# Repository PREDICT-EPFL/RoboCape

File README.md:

# RoboCape

This repository is dedicated to a Beaglebone cape extension developped at EPFL in the Automatic Control Laboratory.
The idea of this platform is to allow the user to transform any mechanically actuated platform, for example a RC car or a quadcopter base, into a robotic vehicle that can be controlled by a remote server.

The repository contains all the design files of the Beaglebone cape extension.
* Schematic
* PCB layout
* Production files
* Documentation files (useful documents and datasheets)

## Finished board

## License

This project is released under the Creative Commons CC-BY-4.0 license.
See http://creativecommons.org/licenses/by/4.0/ for details.

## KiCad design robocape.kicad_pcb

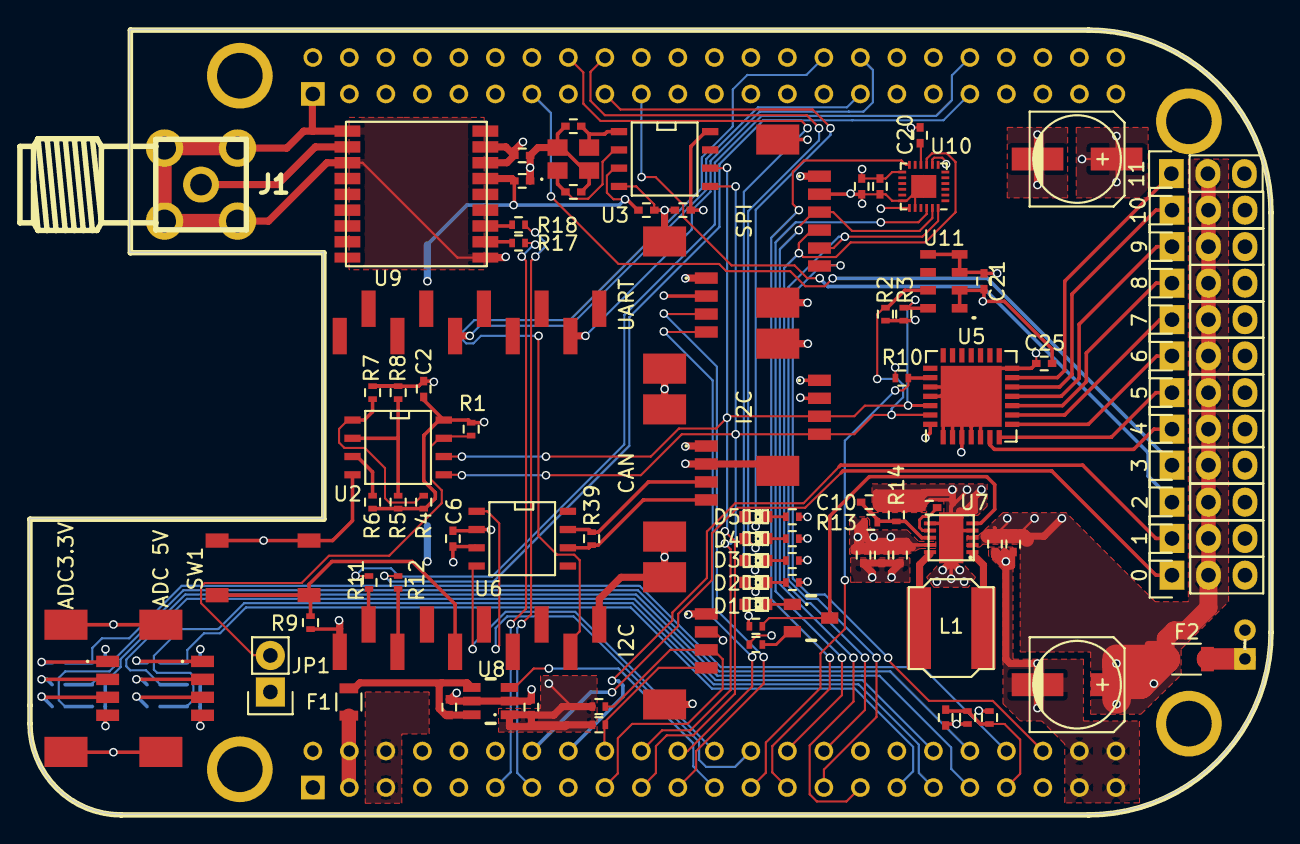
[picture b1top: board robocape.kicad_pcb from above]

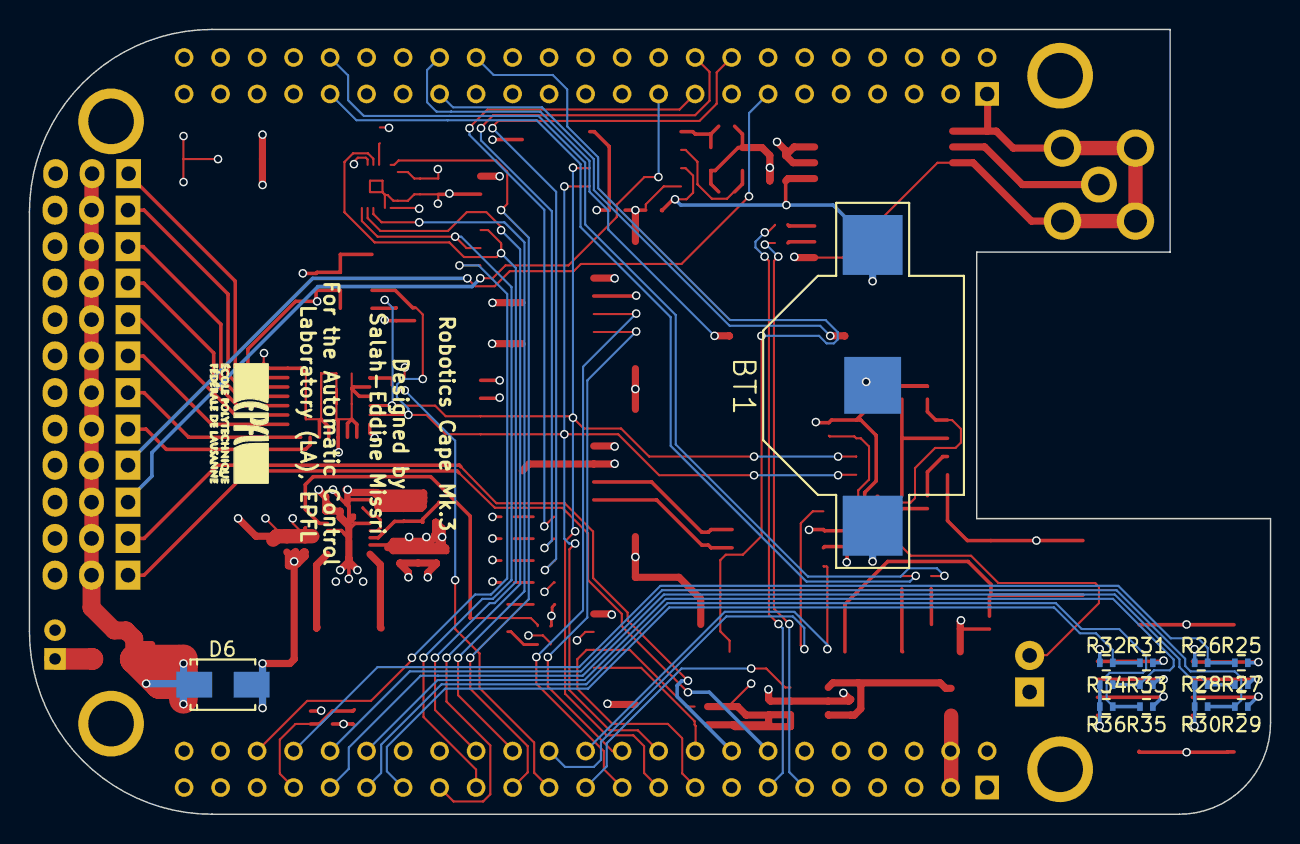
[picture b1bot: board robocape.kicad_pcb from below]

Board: 4 copper layers, 86.4 x 54.6 mm, 110 parts (14 on the bottom side), 85 nets.

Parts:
0, 1, 2, 3, 4, 5, 6, 7, 8, 9, 10, 11: SERVO; Pin_Header_Straight_1x03
BT1: 1.4V to 3.6V; BK-885
C1, C14, C15: 1u; C_0402
C2, C6, C9, C17, C20, C21, C22, C25: 100n; C_0402
C3: 220n; C_0402
C4, C5, C10: 10p; C_0402
C7, C8: 10u; C_0402
C11, C12, C13: 22u; C_0402
C16, C19: 0.1u; C_0402
C18: 10n; C_0402
C23, C24: 100u; c_elec_6.3x7.7
CONN1: UART; _Molex-PicoBlade-SMD-4
CONN5, CONN17: I2C; _Molex-PicoBlade-SMD-4
CONN9: CAN; _Molex-PicoBlade-SMD-4
CONN16: PWR; _Pin2mm_2
CONN18: SPI; _Molex-PicoBlade-SMD-6
CONN19: ADC3.3V; _Molex-PicoBlade-SMD-4
CONN20: ADC 5V; _Molex-PicoBlade-SMD-4
D1: YELLOW; LED-0603
D2: WHITE; LED-0603
D3: GREEN; LED-0603
D4: BLUE; LED-0603
D5: RED; LED-0603
D6: ZENER 12V; Diode-SMA_Standard
F1: 500mA; R_0805
F2: 10A; R_1206
J1: SMA; SMA-CONN
JP1: Jumper_NC_Small; Pin_Header_Straight_1x02
L1: 1uH; Laird_TYS6045
Q1: 2N7002; _SOT23-3
R1, R10: 10k; R_0402
R2, R3, R4, R5, R6, R23, R24, R37: 4.7k; R_0402
R7, R8: 0; R_0402
R9: 50k; R_0402
R11, R12, R17, R18: 330; R_0402
R13, R15: 1M; R_0402
R14: 111k; R_0402
R16, R19, R20, R21, R22: 1k; R_0402
R25, R27, R29: 680; R_0402
R26, R28, R30, R32, R34, R36, R38: 820; R_0402
R31, R33, R35: 1.47k; R_0402
R39: 120; R_0402
SW1: SW_PUSH; _PTS525SK15-SMT-Pushbutton
U1: BEAGLEBONE
U2: CAT24C256W; SOIC-8-N
U3: BQ32000; SOIC-8-N
U4: XBee_Header; Xbee_Header_SMD
U5: PCA9685; QFN-28-1EP_6x6mm_Pitch0.65mm
U6: SN65HVD232D; SOIC-8-N
U7: TPS63060; SON-10
U8: TPS22929D; _TSOT23-6
U9: MAX-M8
U10: MPU-9250; QFN-24-1EP_3x3mm_Pitch0.4mm
U11: MS5611-01BA; _MS5611-01BA
X1: 32768Hz; _TSX-3225-SMD-XTAL

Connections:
+3.3V_A: C1.1, C2.1, C15.1, C17.1, C18.1, C21.1, C25.1, CONN5.1, CONN17.1, D2.2, R1.1, R2.1, R3.1, R4.1, R5.1, R6.1, R10.1, R23.1, R24.1, U2.8, U3.8, U5.28, U8.1, U10.8, U10.13, U10.19, U11.1, U11.2
+3V3: C6.1, C16.1, F1.1, R9.1, U1.C3, U1.C4, U4.1, U6.3, U9.7, U9.8
+5V: C11.1, C12.1, C13.1, CONN1.1, CONN9.1, CONN18.1, D1.2, R13.1, R15.1, U1.C5, U1.C6, U7.9
/Connectivity/ADC_1: R25.2, R26.1, U1.C40
/Connectivity/ADC_2: R27.2, R28.1, U1.C37
/Connectivity/ADC_3: R29.2, R30.1, U1.C38
/Connectivity/ADC_4: R31.2, R32.1, U1.C33
/Connectivity/ADC_5: R33.2, R34.1, U1.C36
/Connectivity/ADC_6: R35.2, R36.1, U1.C35
/Connectivity/CAN_RX: U1.C24, U6.4
/Connectivity/CAN_TX: U1.C26, U6.1
/Connectivity/I2C1_SCL: CONN17.3, R24.2, U1.C17
/Connectivity/I2C1_SDA: CONN17.4, R23.2, U1.C18
/Connectivity/I2C2_SCL: CONN5.3, R3.2, U1.C19, U2.6, U3.6, U5.26, U11.8
/Connectivity/I2C2_SDA: CONN5.4, R2.2, U1.C20, U2.5, U3.5, U5.27, U11.7
/Connectivity/PWMGEN_OE: R10.2, U1.C25, U5.23
/Connectivity/PWM_0: 0.1, U1.C14
/Connectivity/PWM_1: 1.1, U1.C16
/Connectivity/PWM_2: 2.1, U1.B19
/Connectivity/PWM_3: 3.1, U1.B13
/Connectivity/PWM_4: 4.1, U5.6
/Connectivity/PWM_5: 5.1, U5.7
/Connectivity/PWM_6: 6.1, U5.8
/Connectivity/PWM_7: 7.1, U5.9
/Connectivity/PWM_8: 8.1, U5.10
/Connectivity/PWM_9: 9.1, U5.11
/Connectivity/PWM_10: 10.1, U5.12
/Connectivity/PWM_11: 11.1, U5.13
/Connectivity/SPI1_CS1: CONN18.6, U1.C42
/Connectivity/UART_EXT_RX: CONN1.4, U1.C22
/Connectivity/UART_EXT_TX: CONN1.3, U1.C21
/Connectivity/XBEE_CTS: U1.B32, U4.12
/Connectivity/XBEE_DTR: U1.B30, U4.9
/Connectivity/XBEE_RTS: U1.B31, U4.16
/Connectivity/XBEE_RX: R12.1, U1.B37
/Connectivity/XBEE_TX: R11.1, U1.B38
/ERROR_LED: D5.2, U1.B17
/HEARTBEAT_LED: D3.2, U1.B16
/Power/3.3V_A_EN: U1.C23, U8.3
/Power/Back_Bat: BT1.1, C3.1, C19.1, U3.3, U9.6
/Power/PWR_GOOD: Q1.2, R15.2, U7.5
/Power/PWR_VOLTAGE_SENSE: C22.1, R37.2, R38.1, U1.C39
/STATUS_LED: D4.2, U1.B18
/Sensors/GPS_RX: R18.1, U1.C13
/Sensors/GPS_TX: R17.1, U1.C11
/Sensors/MPU9250_CS: U1.C28, U10.22
/Sensors/MPU9250_INT: U1.C27, U10.12
/Sensors/MPU9250_MISO: CONN18.4, U1.C30, U10.9
/Sensors/MPU9250_MOSI: CONN18.5, U1.C29, U10.24
/Sensors/MPU9250_SCK: CONN18.3, U1.C31, U10.23
GND: 0.3, 1.3, 2.3, 3.3, 4.3, 5.3, 6.3, 7.3, 8.3, 9.3, 10.3, 11.3, BT1.2, C1.2, C2.2, C3.2, C4.2, C5.2, C6.2, C7.2, C8.2, C9.2, C10.2, C11.2, C12.2, C13.2, C14.2, C15.2, C16.2, C17.2, C18.2, C19.2, C20.2, C21.2, C22.2, C23.2, C24.2, C25.2, CONN1.2, CONN1.MECH, CONN5.2, CONN5.MECH, CONN9.2, CONN9.MECH, CONN16.2, CONN17.2, CONN17.MECH, CONN18.2, CONN18.MECH, CONN19.4, CONN19.MECH, CONN20.4, CONN20.MECH, D6.2, J1.2, J1.3, J1.4, J1.5, JP1.1, R7.2, R8.2, R14.2, R16.2, R19.1, R20.1, R21.1, R22.1, R26.2, R28.2, R30.2, R32.2, R34.2, R36.2, R38.2, SW1.1, U1.B1, U1.B2, U1.C1, U1.C2, U1.C34, U1.C43, U1.C44, U1.C45, U1.C46, U2.4, U3.4, U4.10, U5.1, U5.2, U5.3, U5.4, U5.5, U5.14, U5.24, U5.25, U5.29, U6.2, U7.4, U7.7, U7.11, U8.2, U8.5, U9.1, U9.10, U9.12, U10.18, U10.20, U10.25, U11.3, U11.4, U11.5, X1.2, X1.4
unnamed: C4.1, U3.2, X1.1
unnamed: C5.1, U3.1, X1.3
unnamed: C9.1, U7.6
unnamed: C10.1, R13.2, R14.1, U7.8
unnamed: C14.1, F1.2, U8.4, U8.6
unnamed: C20.1, U10.10
unnamed: CONN9.3, R39.1, U6.7
unnamed: CONN9.4, R39.2, U6.6
unnamed: CONN16.1, F2.1
unnamed: CONN19.1, R25.1
unnamed: CONN19.2, R27.1
unnamed: CONN19.3, R29.1
unnamed: CONN20.1, R31.1
unnamed: CONN20.2, R33.1
unnamed: CONN20.3, R35.1
unnamed: D1.1, Q1.1
unnamed: D2.1, R19.2
unnamed: D3.1, R20.2
unnamed: D4.1, R21.2
unnamed: D5.1, R22.2
unnamed: J1.1, U9.11
unnamed: JP1.2, R1.2, U2.7
unnamed: L1.1, U7.1
unnamed: L1.2, U7.10
unnamed: Q1.3, R16.1
unnamed: R4.2, R7.1, U2.1
unnamed: R5.2, R8.1, U2.2
unnamed: R6.2, U2.3
unnamed: R9.2, SW1.2, U4.5
unnamed: R11.2, U4.2
unnamed: R12.2, U4.3
unnamed: R17.2, U9.2
unnamed: R18.2, U9.3
POWER: 0.2, 1.2, 2.2, 3.2, 4.2, 5.2, 6.2, 7.2, 8.2, 9.2, 10.2, 11.2, C7.1, C8.1, C23.1, C24.1, D6.1, F2.2, R37.1, U7.2, U7.3

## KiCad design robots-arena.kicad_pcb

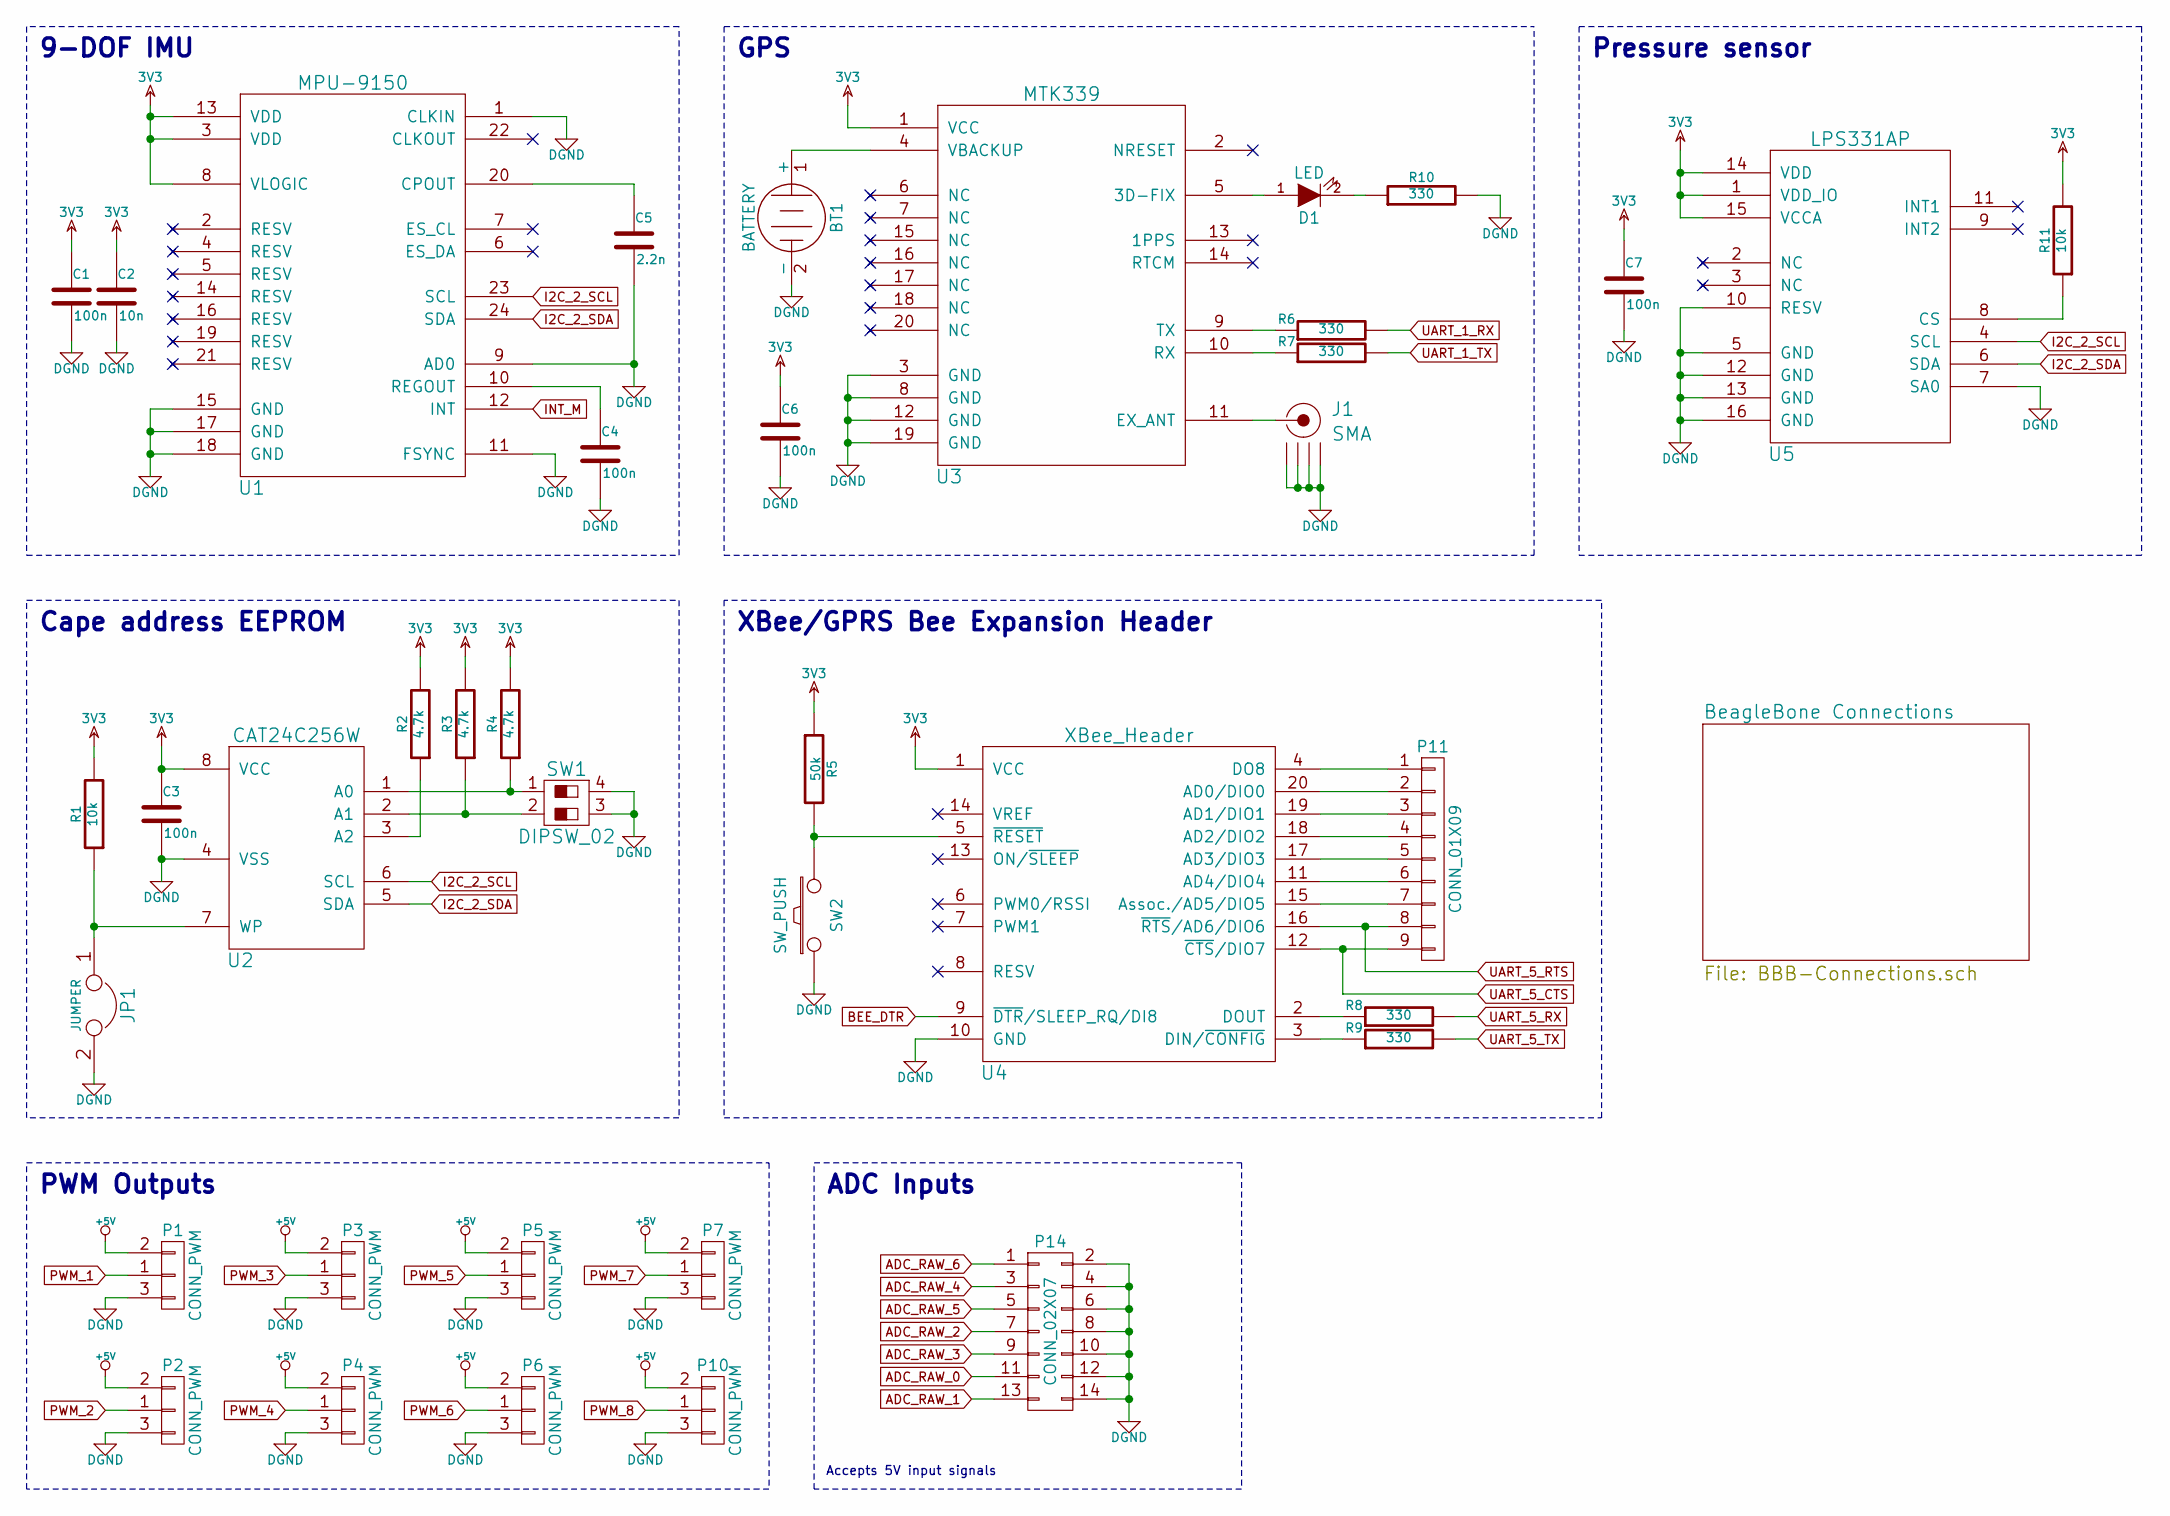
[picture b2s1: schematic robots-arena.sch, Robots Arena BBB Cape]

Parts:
BT1: BATTERY
C1, C3, C4, C6, C7: 100n
C2: 10n
C5: 2.2n
D1: LED
J1: SMA; SMA_antenna
JP1: JUMPER
P1, P2, P3, P4, P5, P6, P7, P10: CONN_PWM
P11: CONN_01X09
P14: CONN_02X07
R1, R11: 10k
R2, R3, R4: 4.7k
R5: 50k
R6, R7, R8, R9, R10: 330
SW1: DIPSW_02
SW2: SW_PUSH
U1: MPU-9150
U2: CAT24C256W
U3: MTK339
U4: XBee_Header
U5: LPS331AP

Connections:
3V3: C1.1, C2.1, C3.1, C6.1, C7.1, R1.2, R2.2, R3.2, R4.2, R5.1, R11.2, U1.3 (VDD), U1.8 (VLOGIC), U1.13 (VDD), U2.8 (VCC), U3.1 (VCC), U4.1 (VCC), U5.1 (VDD_IO), U5.14 (VDD), U5.15 (VCCA); also elsewhere on the board
+5V: P1.2, P2.2, P3.2, P4.2, P5.2, P6.2, P7.2, P10.2; also elsewhere on the board
ADC_RAW_0: P14.11; also elsewhere on the board
ADC_RAW_1: P14.13; also elsewhere on the board
ADC_RAW_2: P14.7; also elsewhere on the board
ADC_RAW_3: P14.9; also elsewhere on the board
ADC_RAW_4: P14.3; also elsewhere on the board
ADC_RAW_5: P14.5; also elsewhere on the board
ADC_RAW_6: P14.1; also elsewhere on the board
BEE_DTR: U4.9 (~DTR~/SLEEP_RQ/DI8); also elsewhere on the board
DGND: BT1.2 (-), C1.2, C2.2, C3.2, C4.2, C5.2, C6.2, C7.2, J1.2 (GND1), J1.3 (GND2), J1.4 (GND3), J1.5 (GND4), JP1.2, P1.3, P2.3, P3.3, P4.3, P5.3, P6.3, P7.3, P10.3, P14.2, P14.4, P14.6, P14.8, P14.10, P14.12, P14.14, R10.2, SW1.3, SW1.4, SW2.1, U1.1 (CLKIN), U1.9 (AD0), U1.11 (FSYNC), U1.15 (GND), U1.17 (GND), U1.18 (GND), U2.4 (VSS), U3.3 (GND), U3.8 (GND), U3.12 (GND), U3.19 (GND), U4.10 (GND), U5.5 (GND), U5.7 (SA0), U5.10 (RESV), U5.12 (GND), U5.13 (GND), U5.16 (GND); also elsewhere on the board
I2C_2_SCL: U1.23 (SCL), U2.6 (SCL), U5.4 (SCL); also elsewhere on the board
I2C_2_SDA: U1.24 (SDA), U2.5 (SDA), U5.6 (SDA); also elsewhere on the board
INT_M: U1.12 (INT); also elsewhere on the board
unnamed: BT1.1 (+), U3.4 (VBACKUP)
unnamed: C4.1, U1.10 (REGOUT)
unnamed: C5.1, U1.20 (CPOUT)
unnamed: D1.1 (A), U3.5 (3D-FIX)
unnamed: D1.2 (K), R10.1
unnamed: J1.1 (RF), U3.11 (EX_ANT)
unnamed: JP1.1, R1.1, U2.7 (WP)
unnamed: P11.1, U4.4 (DO8)
unnamed: P11.2, U4.20 (AD0/DIO0)
unnamed: P11.3, U4.19 (AD1/DIO1)
unnamed: P11.4, U4.18 (AD2/DIO2)
unnamed: P11.5, U4.17 (AD3/DIO3)
unnamed: P11.6, U4.11 (AD4/DIO4)
unnamed: P11.7, U4.15 (Assoc./AD5/DIO5)
unnamed: R2.1, U2.3 (A2)
unnamed: R3.1, SW1.2, U2.2 (A1)
unnamed: R4.1, SW1.1, U2.1 (A0)
unnamed: R5.2, SW2.2, U4.5 (~RESET)
unnamed: R6.1, U3.9 (TX)
unnamed: R7.1, U3.10 (RX)
unnamed: R8.1, U4.2 (DOUT)
unnamed: R9.1, U4.3 (DIN/~CONFIG)
unnamed: R11.1, U5.8 (CS)
PWM_1: P1.1; also elsewhere on the board
PWM_2: P2.1; also elsewhere on the board
PWM_3: P3.1; also elsewhere on the board
PWM_4: P4.1; also elsewhere on the board
PWM_5: P5.1; also elsewhere on the board
PWM_6: P6.1; also elsewhere on the board
PWM_7: P7.1; also elsewhere on the board
PWM_8: P10.1; also elsewhere on the board
UART_1_RX: R6.2; also elsewhere on the board
UART_1_TX: R7.2; also elsewhere on the board
UART_5_CTS: P11.9, U4.12 (~CTS~/DIO7); also elsewhere on the board
UART_5_RTS: P11.8, U4.16 (~RTS~/AD6/DIO6); also elsewhere on the board
UART_5_RX: R8.2; also elsewhere on the board
UART_5_TX: R9.2; also elsewhere on the board

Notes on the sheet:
Cape address EEPROM
9-DOF IMU
GPS
Pressure sensor
PWM Outputs
XBee/GPRS Bee Expansion Header
ADC Inputs
Accepts 5V input signals

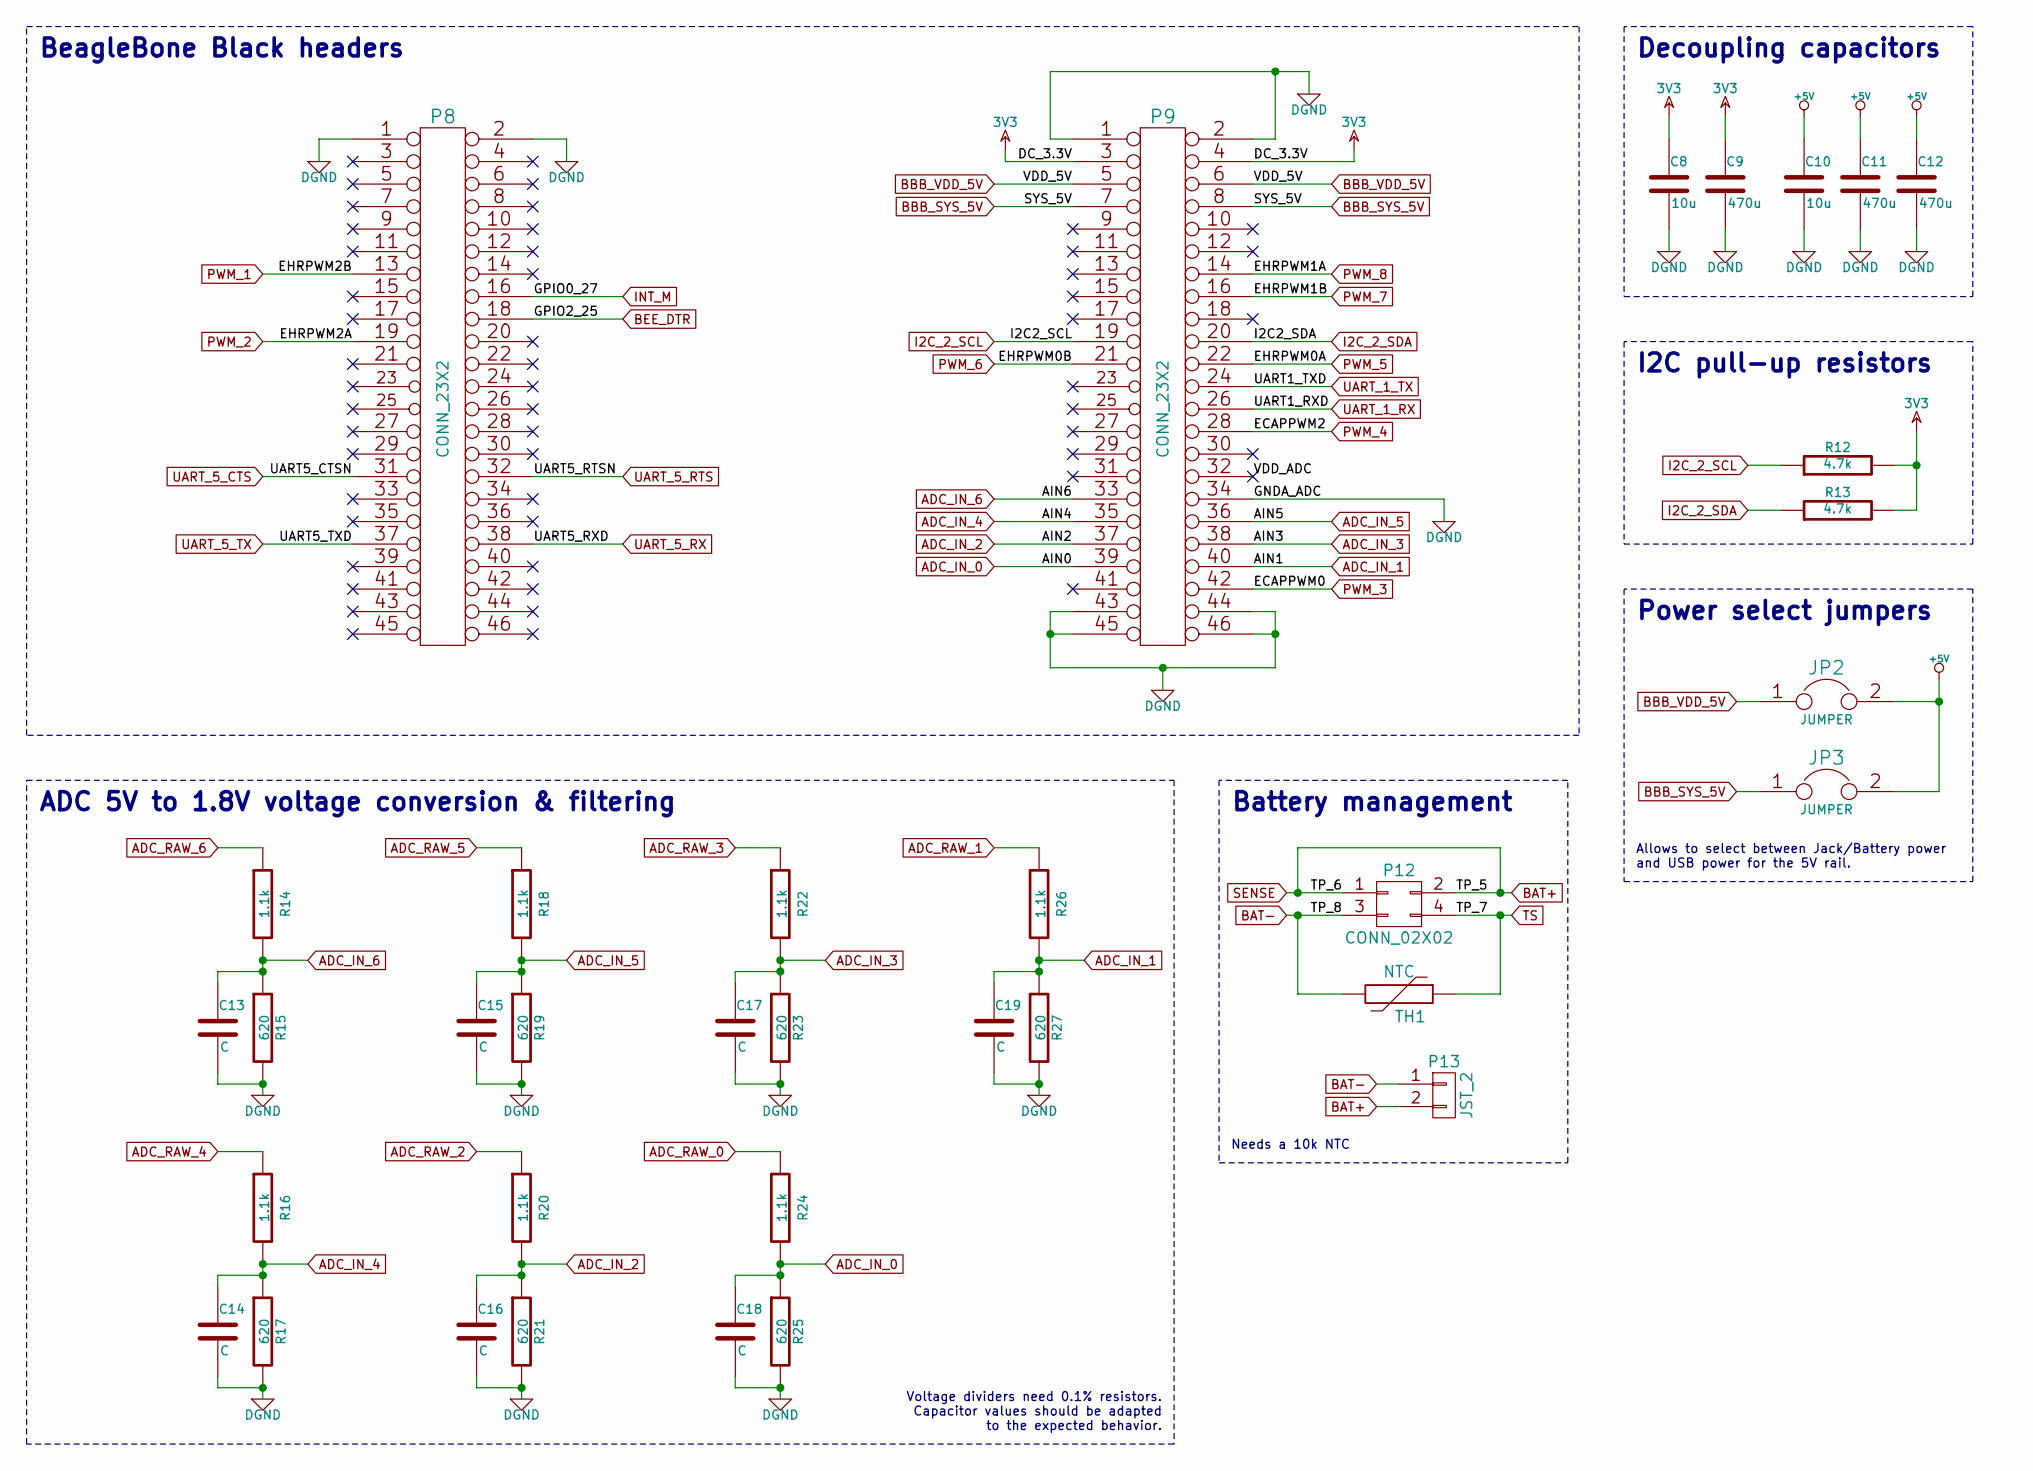
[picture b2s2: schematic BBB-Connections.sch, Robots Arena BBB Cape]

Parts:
C8, C10: 10u
C9, C11, C12: 470u
C13, C14, C15, C16, C17, C18, C19: C
JP2, JP3: JUMPER
P8, P9: CONN_23X2
P12: CONN_02X02
P13: JST_2
R12, R13: 4.7k
R14, R16, R18, R20, R22, R24, R26: 1.1k
R15, R17, R19, R21, R23, R25, R27: 620
TH1: NTC

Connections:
3V3: C8.1, C9.1, P9.3, P9.4, R12.2, R13.2; also elsewhere on the board
+5V: C10.1, C11.1, C12.1, JP2.2, JP3.2; also elsewhere on the board
/BeagleBone Connections/VDD_ADC: P9.32
ADC_IN_0: C18.1, P9.39, R24.2, R25.1
ADC_IN_1: C19.1, P9.40, R26.2, R27.1
ADC_IN_2: C16.1, P9.37, R20.2, R21.1
ADC_IN_3: C17.1, P9.38, R22.2, R23.1
ADC_IN_4: C14.1, P9.35, R16.2, R17.1
ADC_IN_5: C15.1, P9.36, R18.2, R19.1
ADC_IN_6: C13.1, P9.33, R14.2, R15.1
ADC_RAW_0: R24.1; also elsewhere on the board
ADC_RAW_1: R26.1; also elsewhere on the board
ADC_RAW_2: R20.1; also elsewhere on the board
ADC_RAW_3: R22.1; also elsewhere on the board
ADC_RAW_4: R16.1; also elsewhere on the board
ADC_RAW_5: R18.1; also elsewhere on the board
ADC_RAW_6: R14.1; also elsewhere on the board
BAT+: P12.1, P12.2, P13.2 (BAT+)
BAT-: P12.3, P13.1 (BAT-), TH1.2
BBB_SYS_5V: JP3.1, P9.7, P9.8
BBB_VDD_5V: JP2.1, P9.5, P9.6
BEE_DTR: P8.18; also elsewhere on the board
DGND: C8.2, C9.2, C10.2, C11.2, C12.2, C13.2, C14.2, C15.2, C16.2, C17.2, C18.2, C19.2, P8.1, P8.2, P9.1, P9.2, P9.34, P9.43, P9.44, P9.45, P9.46, R15.2, R17.2, R19.2, R21.2, R23.2, R25.2, R27.2; also elsewhere on the board
I2C_2_SCL: P9.19, R12.1; also elsewhere on the board
I2C_2_SDA: P9.20, R13.1; also elsewhere on the board
INT_M: P8.16; also elsewhere on the board
PWM_1: P8.13; also elsewhere on the board
PWM_2: P8.19; also elsewhere on the board
PWM_3: P9.42; also elsewhere on the board
PWM_4: P9.28; also elsewhere on the board
PWM_5: P9.22; also elsewhere on the board
PWM_6: P9.21; also elsewhere on the board
PWM_7: P9.16; also elsewhere on the board
PWM_8: P9.14; also elsewhere on the board
TS: P12.4, TH1.1
UART_1_RX: P9.26; also elsewhere on the board
UART_1_TX: P9.24; also elsewhere on the board
UART_5_CTS: P8.31; also elsewhere on the board
UART_5_RTS: P8.32; also elsewhere on the board
UART_5_RX: P8.38; also elsewhere on the board
UART_5_TX: P8.37; also elsewhere on the board

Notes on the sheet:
I2C pull-up resistors
Decoupling capacitors
BeagleBone Black headers
Power select jumpers
Battery management
ADC 5V to 1.8V voltage conversion & filtering
Voltage dividers need 0.1% resistors. Capacitor values should be adapted to the expected behavior.
Allows to select between Jack/Battery power and USB power for the 5V rail.
Needs a 10k NTC

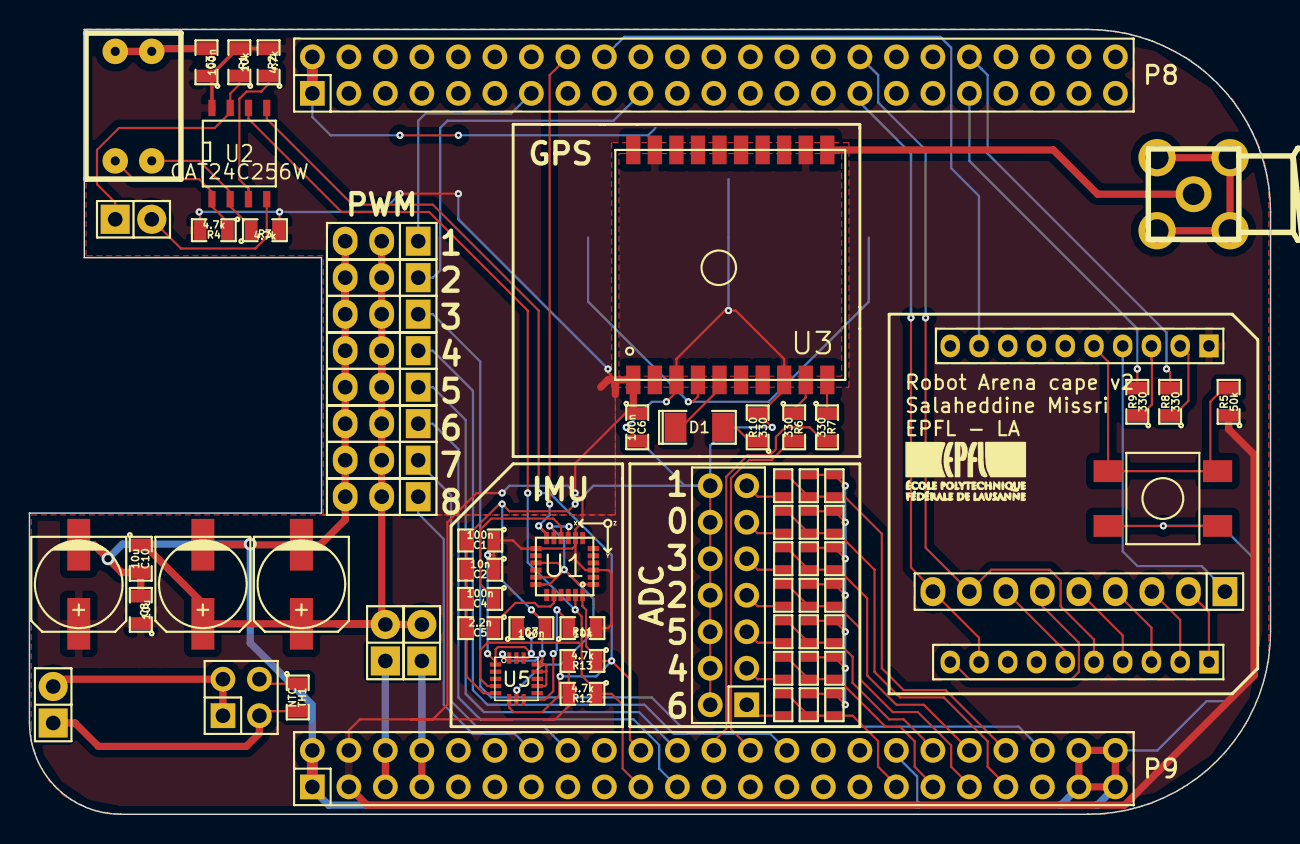
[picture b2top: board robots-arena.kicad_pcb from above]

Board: 2 copper layers, 86.4 x 54.6 mm, 74 parts (1 on the bottom side), 63 nets.

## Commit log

2014-11-10 v0.1 of the cape, tested and working
2014-11-22 organisation restructuration
2014-11-22 adding datasheets
2014-11-23 restructuration of components & schematic
2014-11-23 added readme file
2014-11-23 pdf update
2014-11-24 added bat mgmt, pwr select, xbee header
2014-11-25 .sch done, .net done, components on PCB done
2014-11-25 layout in progress, corrected pwm order
2014-11-29 Added adc connectors w/ 5 to 1.8V conversion
2014-11-29 Added comments on the schematics
2014-11-29 Update netlist & components footprints
2014-11-29 Place components on PCB & ajust nets to stay w/ 2 layers
2014-11-29 Layout completed
2014-11-29 Gerber files generated
2014-12-05 Complete readme file
2014-12-25 Correct XBee header & Update layout and Gerber files
2014-12-31 Update readme file
2015-01-02 Add BOM with Digikey links & price calculation
2015-07-14 Add Kicad library as submodule
2015-07-14 Project initial setup
2015-07-14 Schematic: EEPROM + IMU
2015-07-14 Schematic: Barometer
2015-07-15 Schematic: Xbee header
2015-07-16 Schematics: PWM
2015-07-18 Schematics: CAN
2015-07-18 Schematics: Power supply from battery input
2015-07-20 Schematics: GPS, Backup battery & Load Switch
2015-07-20 Schematics: Additional connectors (ADC, I2C, UART)
2015-07-20 Schematics: RTC
2015-07-20 Schematics: Minor cleanups
2015-07-20 Schematics: LEDs
2015-07-20 Schematics: Additional I2C connector
2015-07-20 Schematics: Missing I2C1 pull-ups
2015-07-20 Schematics: SPI connector
2015-07-20 Schematics: Minor cleanups & ADC split between 3.3V & 5V
2015-07-20 Schematics: Power input overvoltage protection
2015-07-20 Netlist
2015-07-21 Schematics: CAN termination resistor + PWM gen decoupling cap
2015-07-21 PCB: Components placed
2015-07-22 PCB: Layout of close tracks
2015-07-22 PCB: 3v3 zone fill in power plane + 3v3 wiring
2015-07-23 PCB: PWM silkscreen & some 3d models
2015-07-23 PCB: Correct footprint and layout of 5V regulator
    Also added some 3D models (GPS, SMA)
2015-07-23 PCB: More tracks
2015-07-23 PCB: More and more tracks
2015-07-24 PCB: Done
2015-07-24 Schematics in pdf format
2015-07-24 Gerber production files
2015-07-24 Datasheets
2015-08-11 Correct GPS schematic/layout to account for active antenna
2015-09-16 Clean up readme
2015-09-16 Add license
2015-09-16 Add pictures in readme to show the board
